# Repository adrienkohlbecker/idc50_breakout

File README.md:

# IDC 50 breakout

## Board

## Schematic

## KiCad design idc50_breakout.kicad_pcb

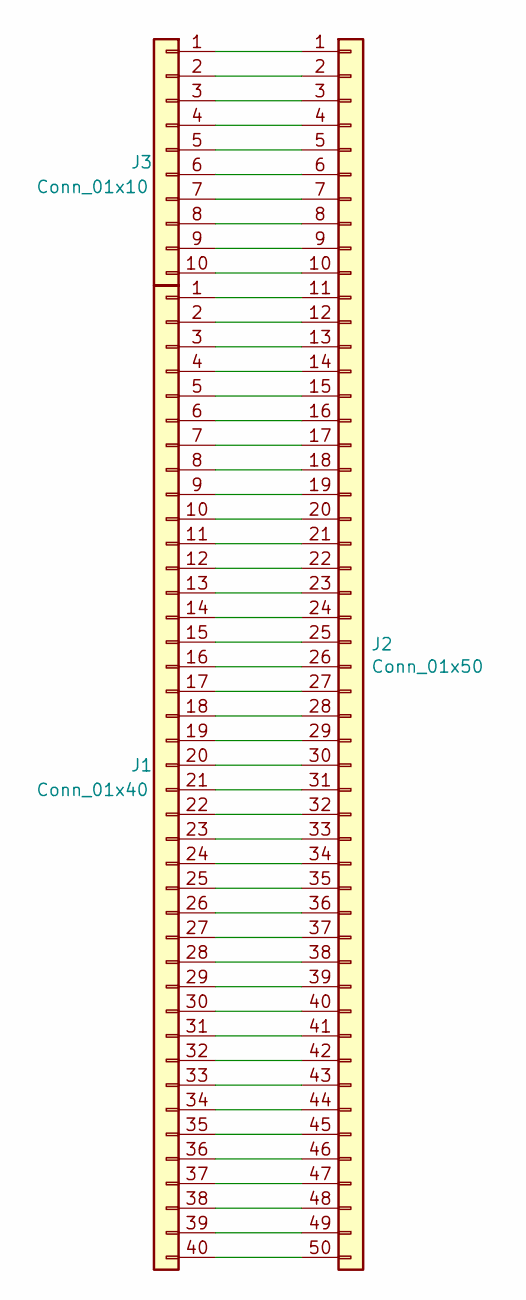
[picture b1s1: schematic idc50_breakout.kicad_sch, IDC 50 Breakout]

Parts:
J1: Conn_01x40; PinSocket_1x40_P2.54mm_Vertical
J2: Conn_01x50; IDC-Header_2x25_P2.54mm_Vertical
J3: Conn_01x10; PinSocket_1x10_P2.54mm_Vertical

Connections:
unnamed: J1.1, J2.11
unnamed: J1.2, J2.12
unnamed: J1.3, J2.13
unnamed: J1.4, J2.14
unnamed: J1.5, J2.15
unnamed: J1.6, J2.16
unnamed: J1.7, J2.17
unnamed: J1.8, J2.18
unnamed: J1.9, J2.19
unnamed: J1.10, J2.20
unnamed: J1.11, J2.21
unnamed: J1.12, J2.22
unnamed: J1.13, J2.23
unnamed: J1.14, J2.24
unnamed: J1.15, J2.25
unnamed: J1.16, J2.26
unnamed: J1.17, J2.27
unnamed: J1.18, J2.28
unnamed: J1.19, J2.29
unnamed: J1.20, J2.30
unnamed: J1.21, J2.31
unnamed: J1.22, J2.32
unnamed: J1.23, J2.33
unnamed: J1.24, J2.34
unnamed: J1.25, J2.35
unnamed: J1.26, J2.36
unnamed: J1.27, J2.37
unnamed: J1.28, J2.38
unnamed: J1.29, J2.39
unnamed: J1.30, J2.40
unnamed: J1.31, J2.41
unnamed: J1.32, J2.42
unnamed: J1.33, J2.43
unnamed: J1.34, J2.44
unnamed: J1.35, J2.45
unnamed: J1.36, J2.46
unnamed: J1.37, J2.47
unnamed: J1.38, J2.48
unnamed: J1.39, J2.49
unnamed: J1.40, J2.50
unnamed: J2.1, J3.1
unnamed: J2.2, J3.2
unnamed: J2.3, J3.3
unnamed: J2.4, J3.4
unnamed: J2.5, J3.5
unnamed: J2.6, J3.6
unnamed: J2.7, J3.7
unnamed: J2.8, J3.8
unnamed: J2.9, J3.9
unnamed: J2.10, J3.10

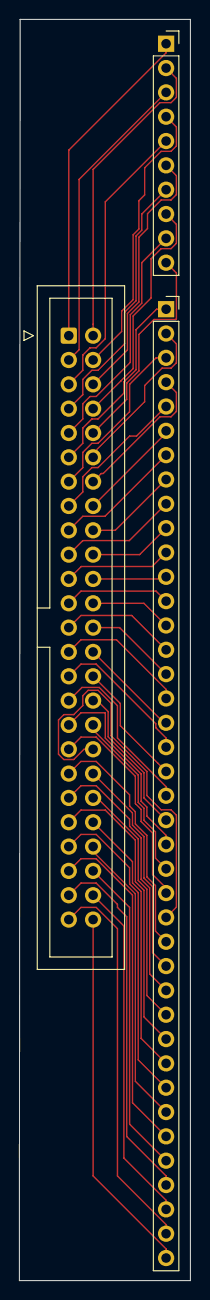
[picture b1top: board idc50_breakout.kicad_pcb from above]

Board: 2 copper layers, 17.9 x 131.7 mm, 3 parts (0 on the bottom side), 50 nets.

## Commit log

2021-11-19 Add idc50 breakout
2021-12-19 Remove ignored files
2023-06-07 Updte for KiCad 6
